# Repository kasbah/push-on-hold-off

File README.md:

See a preview of the board and buy the parts from the [kitspace.org page](https://kitspace.org/boards/github.com/kasbah/push-on-hold-off/). 

A power switch using a push button. It turns on with a single press and only turns off when you hold the button down. This could be used to get functionality similar to most laptops where a single press when on will initiate a "soft" shutdown but you can force a "hard" shutdown by holding it down.

The circuit is from [this article](http://www.mosaic-industries.com/embedded-systems/microcontroller-projects/electronic-circuits/push-button-switch-turn-on/latching-toggle-power-switch#press-on-hold-off-latching-circuits).

The board is my own design and features:

- Standard 0.1" spacing, fits neatly onto a breadboard
- On-board button (and pins to connect your own)
- Two LEDs indicate input and output power
- Configurable to automatically turn on or stay off on initial power through a solder jumper (auto-off is the default)
- Can switch 3-20V and up to 4A

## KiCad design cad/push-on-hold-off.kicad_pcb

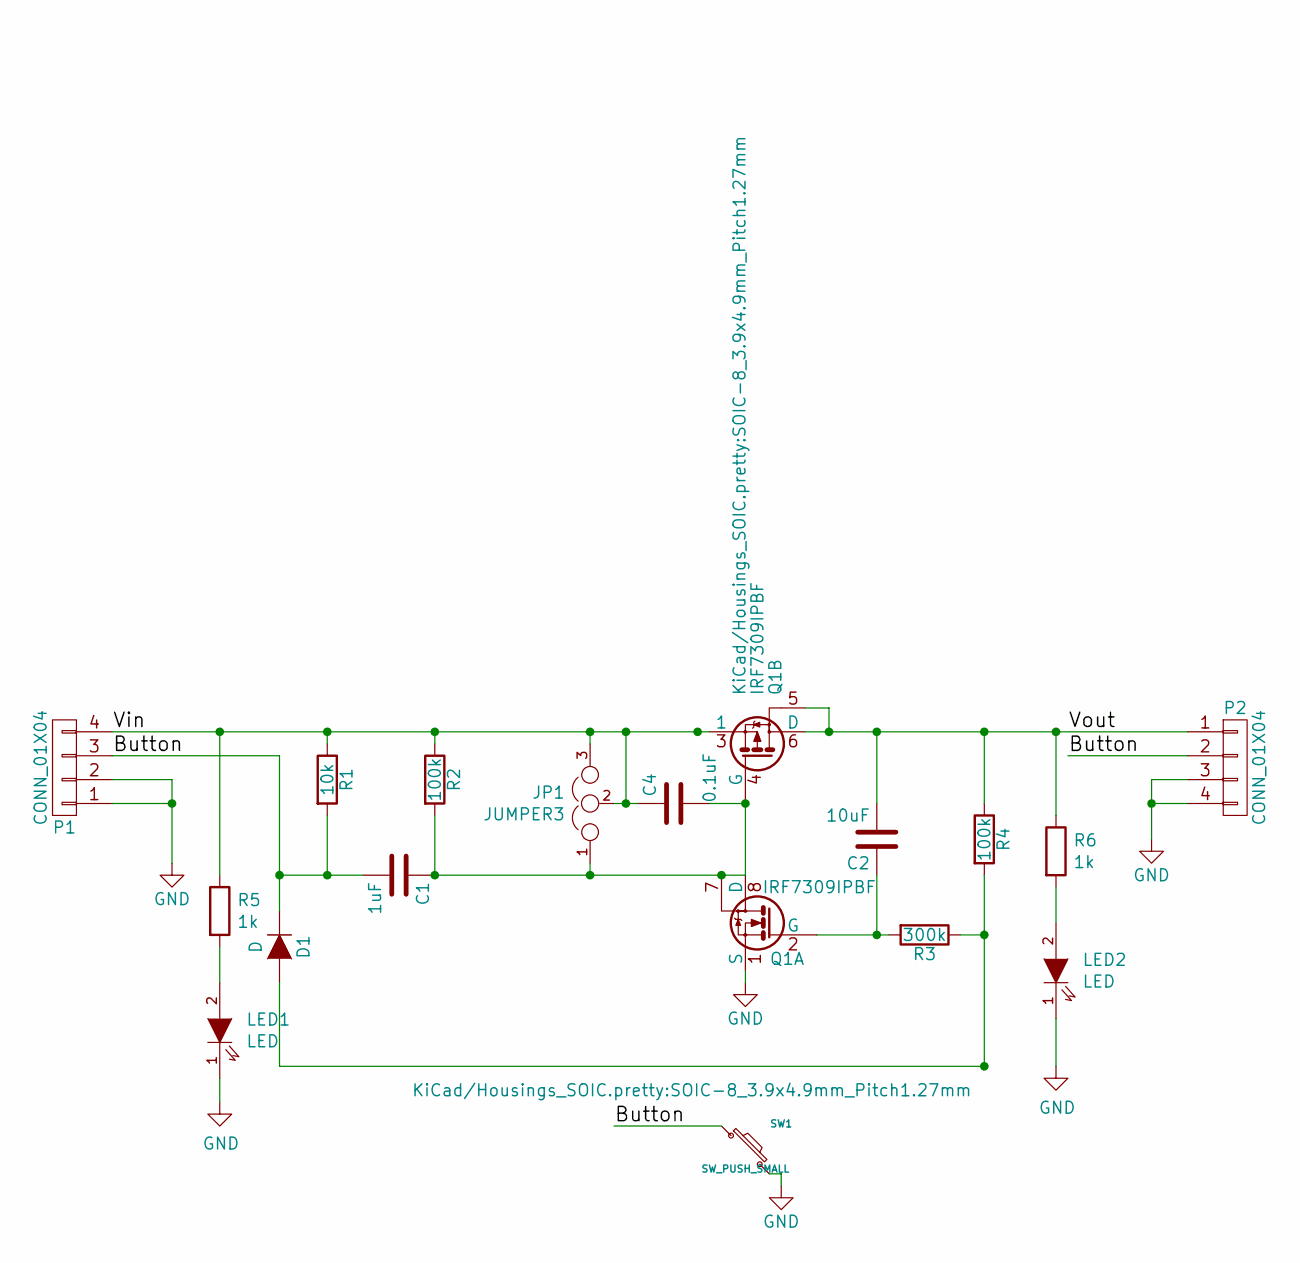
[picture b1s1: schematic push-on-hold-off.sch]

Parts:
C1: 1uF; C_0603_HandSoldering
C2: 10uF; C_0603_HandSoldering
C4: 0.1uF; C_0603_HandSoldering
D1: D; MiniMELF_Handsoldering
JP1: JUMPER3; SOLDER-JUMPER_2-WAY
LED1, LED2: LED; R_0603_HandSoldering
P1, P2: CONN_01X04; Pin_Header_Straight_1x04
Q1: IRF7309IPBF; SOIC-8_3.9x4.9mm_Pitch1.27mm
R1: 10k; R_0603_HandSoldering
R2, R4: 100k; R_0603_HandSoldering
R3: 300k; R_0603_HandSoldering
R5, R6: 1k; R_0603_HandSoldering
SW1: SW_PUSH_SMALL; FSM2JSMA

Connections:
/Button: C1.2, D1.1 (K), P1.3, P2.2, R1.2, SW1.1
/Vin: C4.1, JP1.2, JP1.3, P1.4, Q1.3 (1), R1.1, R2.1, R5.1
/Vout: C2.2, P2.1, Q1.5, Q1.6 (D), R4.1, R6.1
GND: LED1.1 (K), LED2.1 (K), P1.1, P1.2, P2.3, P2.4, Q1.1 (S), SW1.2
unnamed: C1.1, C4.2, JP1.1, Q1.4 (G), Q1.7, Q1.8 (D), R2.2
unnamed: C2.1, Q1.2 (G), R3.2
unnamed: D1.2 (A), R3.1, R4.2
unnamed: LED1.2 (A), R5.2
unnamed: LED2.2 (A), R6.2

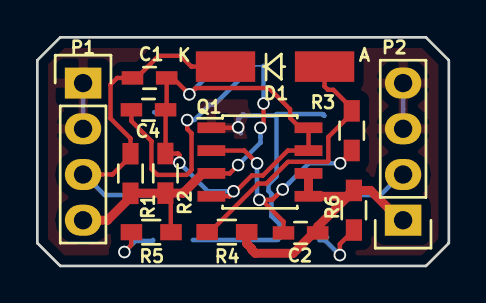
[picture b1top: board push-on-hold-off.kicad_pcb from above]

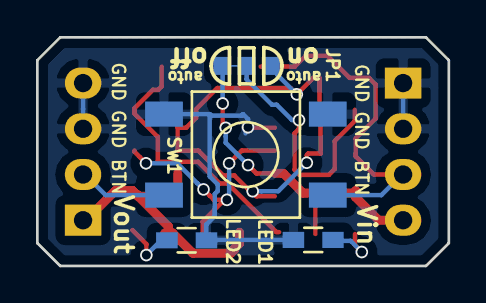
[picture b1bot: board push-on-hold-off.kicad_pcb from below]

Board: 2 copper layers, 22.9 x 12.7 mm, 17 parts (4 on the bottom side), 9 nets.

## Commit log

2016-01-20 Annotate schematic
2016-01-20 Start layout
2016-01-20 Do some placing and draw outline
2016-01-20 Route most components
2016-01-20 Finish routing, add fills
2016-01-20 Add BOM, gerbers and kitnic.yaml
2016-01-20 Plot outline
2016-01-20 Add silkscreen connection reference
2016-01-20 Adjust gnd reference
2016-01-20 Specify license
2016-01-26 Increase vias to 0.5mm drill with 0.7mm pad
2016-05-13 Rename BOM to bom
2016-06-07 Add auto/on off caps and change Q1 footprint
2016-06-07 Switch diode to bigger package
2016-06-07 Add a jumper to configure auto on/off
2016-06-09 Use custom footprint paths and add LEDs
2016-06-09 Switch button footprint to match BOM
2016-06-09 Sort button-side of board
2016-06-10 Switch diode to a mini-melf
2016-06-10 Route the board
2016-06-10 Sort out silkscreen and plot
2016-06-10 Switch rendering colour for kitnic
2016-06-10 Re-plot with new ex
2016-06-10 Re-plot with protel extensions
2016-06-10 Get rid of old csv
2016-06-11 Update BOM
2016-06-11 Extract bom into schematic
2016-06-30 Fix auto-on jumper which was supposed to be to ground
2016-06-30 Re-plot gerbers
2016-08-14 Add more info to README
2017-05-21 Add kitnic link to README
2022-06-21 Rename kitnic.yaml to kitspace.yaml
2022-06-21 Update bill of materials
2024-10-11 Add LCSC part numbers
2024-10-11 Add LCSC part numbers (#7)
